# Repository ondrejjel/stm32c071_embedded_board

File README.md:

# STM32C071 Development Board

A compact, portable embedded development board built around the **STM32C071K8T6** microcontroller.

The board was designed as a personal platform for embedded firmware development, hardware experimentation, and prototyping. The focus is on providing a reasonably complete development environment in a small form factor while keeping important interfaces accessible for debugging and experimentation.

> **Status:** Rev. 1 PCB manufactured.

## Features

### MCU

* **STM32C071K8T6**
* ARM Cortex-M0+ core
* LQFP-32 package
* SWD programming and debugging
* Dedicated RESET and BOOT0 buttons

### Memory

* **16 MB SPI NOR flash**
* Winbond **W25Q128JV**
* Dedicated SPI interface
* Accessible through exposed test points

### Security

* **ATECC608A** secure element
* I²C interface
* Intended for experimentation with hardware-backed cryptography, secure key storage, and device identity

### USB

* USB-C receptacle
* USB 2.0 interface
* **USBLC6-4SC6** ESD protection

### Power

* 5 V input
* **MCP1825S-330** 3.3 V LDO
* Exposed 5 V and 3.3 V test points
* Multiple ground test points

### User Interface

* 5 user buttons
* Dedicated RESET button
* Dedicated BOOT0 button
* Dedicated red power indicator LED
* 5 user LEDs:

  * 1× red
  * 1× green
  * 1× blue
  * 1× orange
  * 1× yellow

### Debugging & Test

The board includes numerous test points to make hardware bring-up and debugging easier.

Exposed signals include:

* SWDIO
* SWCLK
* NRST
* BOOT0
* UART TX/RX
* SPI CS
* SPI CLK
* SPI DI
* SPI DO
* I²C SDA/SCL
* 5 V
* 3.3 V
* GND

An **STDC14** debug connector is also provided.

## Hardware Architecture

The main hardware blocks are:

```text
                         ┌──────────────────┐
                    -----│    USB-C Input   │
                    │    └────────┬─────────┘
                    │             │
                   USB           5 V
                    │             │
                    │    ┌────────▼─────────┐
                    │    │   Power / 3.3 V  │
                    │    │     MCP1825S     │
                    │    └────────┬─────────┘
                    │             │ 
                 ┌──▼─────────────▼────────────────┐
                 │          STM32C071K8T6           │
                 │                                 │
                 │  GPIO   SPI   I²C   USB   SWD   │
                 └───┬─────┬─────┬─────┬────┬─────┘
                     │     │     │     │    │
                     │     │     │     │    └── Debug
                     │     │     │     │
                     │     │     │     └──── USB
                     │     │     │
                     │     │     └──────── ATECC608A
                     │     │
                     │     └────────────── W25Q128JV
                     │
                     └────────────────── Buttons / LEDs
```

The exact peripheral assignments are defined in the schematic and firmware configuration.

## PCB Design

The schematic and PCB were designed entirely in **KiCad**.

The board was designed around several goals:

* compact and portable form factor
* practical access to debugging interfaces
* dedicated test points for important signals
* integrated external memory
* hardware security experimentation
* simple power architecture
* useful user I/O
* easy hardware bring-up

The PCB was manufactured by **JLCPCB**.

## Bring-up Plan

Once the assembled board is available, hardware bring-up will be performed incrementally.

### 1. Power

* Inspect the assembled PCB
* Check for shorts before applying power
* Verify 5 V input
* Verify 3.3 V regulator output
* Measure idle current consumption

### 2. MCU

* Connect through SWD
* Verify MCU identification
* Test RESET
* Verify BOOT0 operation
* Flash a minimal test program

### 3. GPIO

* Test user buttons
* Test LEDs
* Verify GPIO levels and mappings

### 4. SPI Flash

* Verify SPI signals with a logic analyzer
* Read the JEDEC ID
* Test read/write operations
* Verify the full memory interface

### 5. I²C / Secure Element

* Verify I²C electrical levels
* Detect the ATECC608A
* Establish communication
* Test basic device functionality

### 6. USB

* Verify USB power and signal integrity
* Test USB enumeration
* Develop and validate the intended USB functionality

Any hardware problems discovered during bring-up will be documented in this repository.

## Test Points

The board intentionally exposes important signals for external measurement.

| Signal     | Purpose              |
| ---------- | -------------------- |
| GND        | Ground reference     |
| 5V         | Main 5 V rail        |
| 3V3        | Regulated 3.3 V rail |
| NRST       | MCU reset            |
| BOOT0      | Boot configuration   |
| SWDIO      | SWD data             |
| SWCLK      | SWD clock            |
| TX         | UART transmit        |
| RX         | UART receive         |
| CS         | SPI chip select      |
| CLK        | SPI clock            |
| DI         | SPI data input       |
| DO         | SPI data output      |
| SDA        | I²C data             |
| SCL        | I²C clock            |
| USERBTN1–5 | User button signals  |

## Repository Structure

```text
.
├── hardware/
│   ├── schematic/
│   ├── pcb/
│   └── fabrication/
├── firmware/
├── docs/
├── LICENSE
└── README.md
```

The structure may evolve as firmware and documentation are added.

## Design Files

The KiCad project contains the complete schematic and PCB design.

Manufacturing files are included so that future revisions can be reproduced or modified.

## Bill of Materials

The main active components are:

| Reference | Component       | Purpose                     |
| --------- | --------------- | --------------------------- |
| U1        | STM32C071K8T6   | Main MCU                    |
| U2        | ATECC608A-SSHDA | Secure element              |
| U3        | W25Q128JV       | 16 MB SPI flash             |
| U4        | USBLC6-4SC6     | USB ESD protection          |
| U5        | MCP1825S-330E   | 3.3 V LDO                   |
| J1        | STDC14          | Debug/programming connector |
| J2        | USB-C           | USB/power connection        |

The complete BOM is available in the hardware project files.

## Project Status

| Area                | Status                |
| ------------------- | --------------------- |
| Schematic           | Complete              |
| PCB layout          | Complete              |
| Manufacturing files | Complete              |
| PCB manufacturing   | In progress           |
| Assembly            | Pending               |
| Hardware bring-up   | Pending               |
| Firmware            | Planned               |

## Lessons & Revision History

This is my first custom PCB project, so the first revision is also intended as a learning platform.

Rather than treating Rev. 1 as a final design, the goal is to use the board to identify:

* schematic mistakes
* layout issues
* component selection problems
* power-related issues
* signal integrity problems
* usability improvements

Findings from the first hardware revision will be documented here and used to guide future revisions.

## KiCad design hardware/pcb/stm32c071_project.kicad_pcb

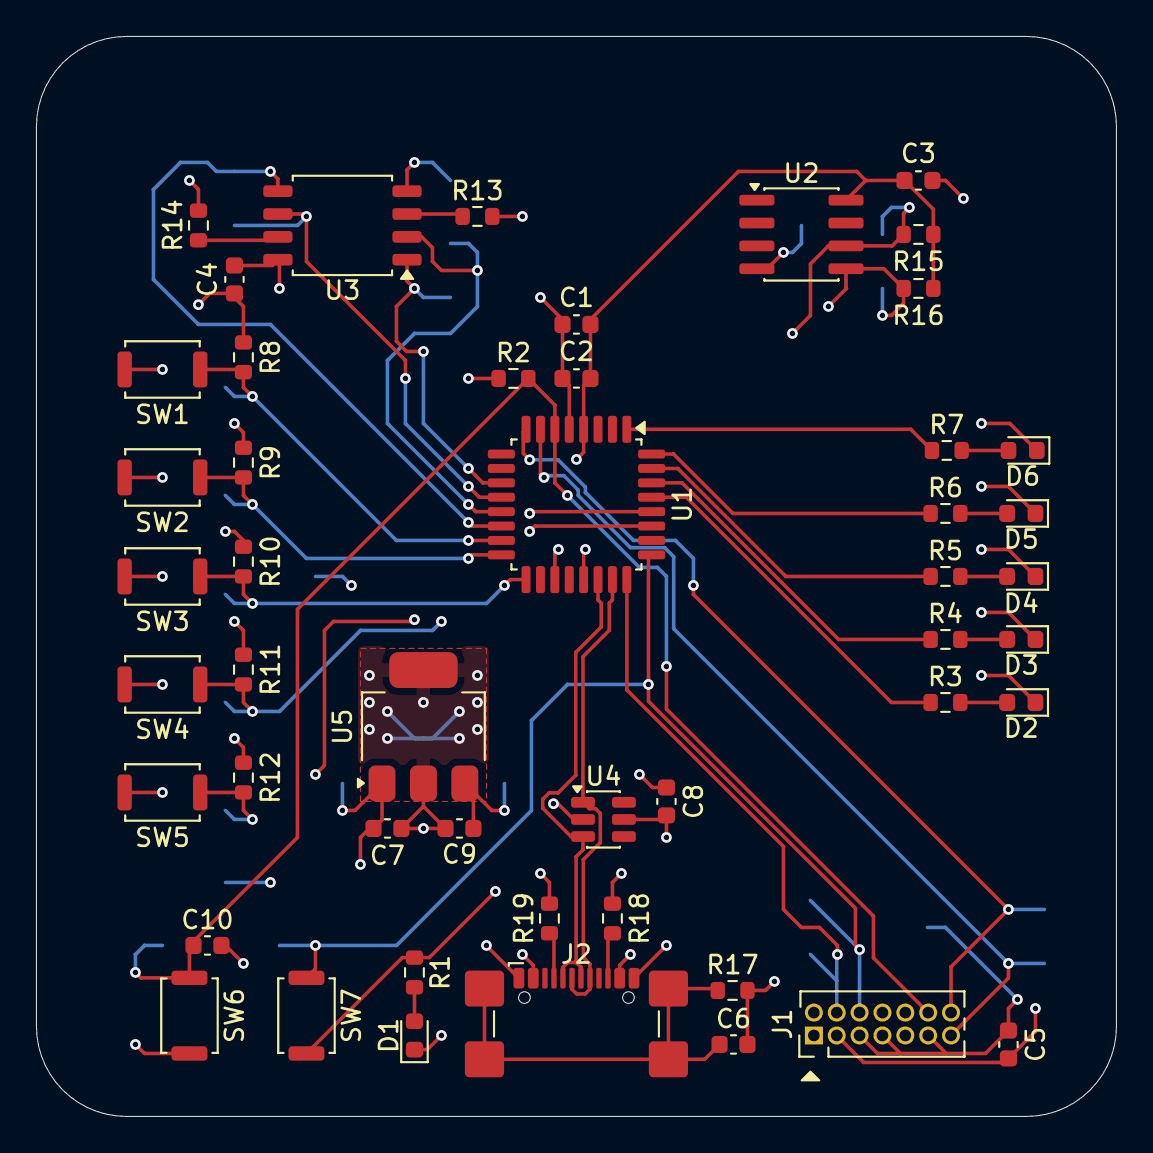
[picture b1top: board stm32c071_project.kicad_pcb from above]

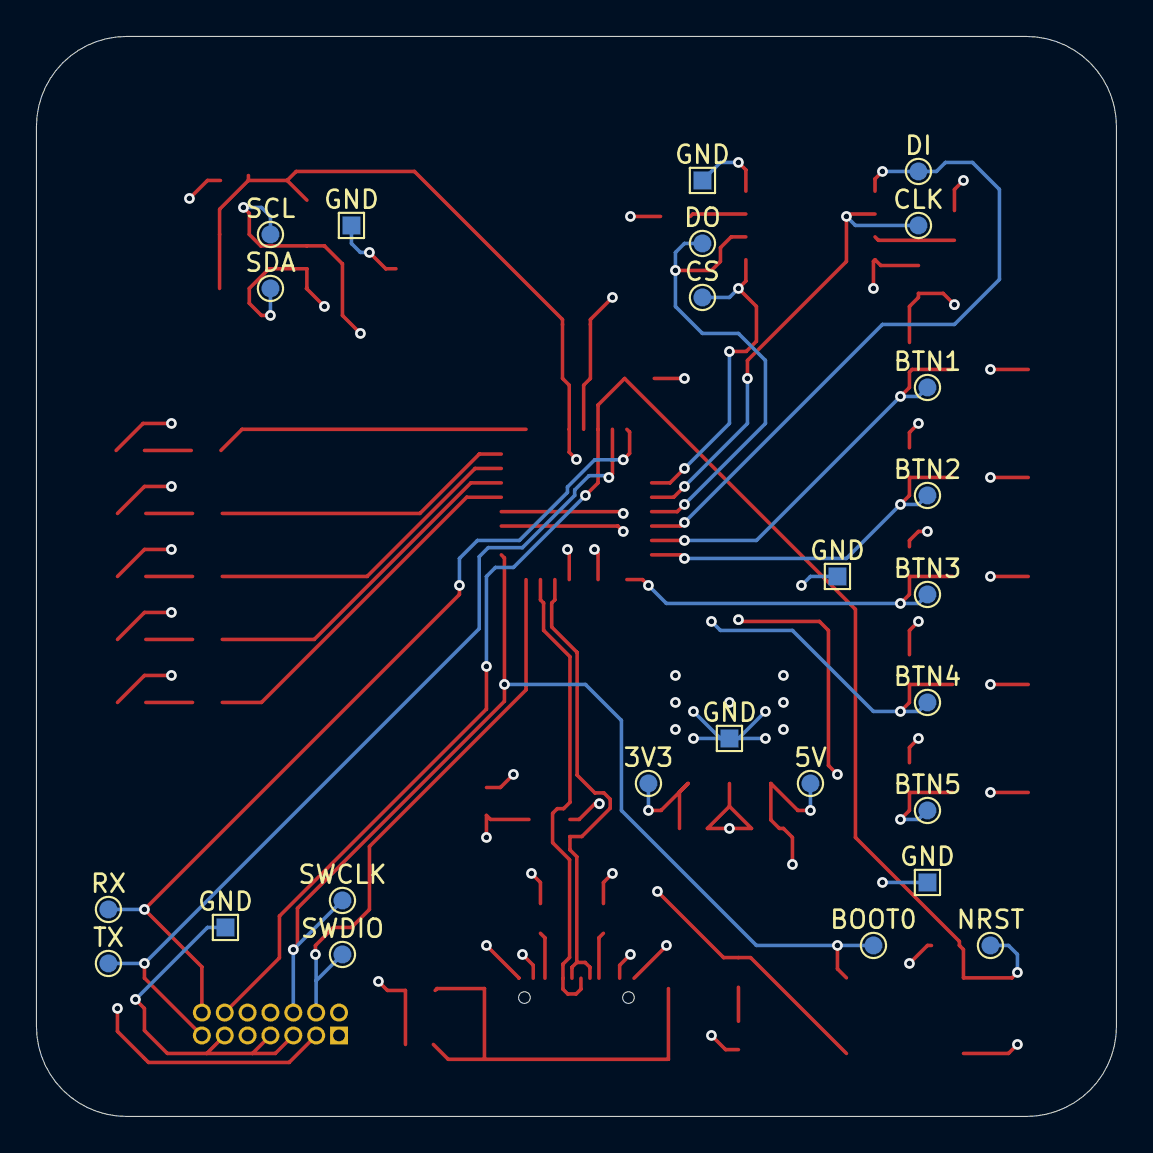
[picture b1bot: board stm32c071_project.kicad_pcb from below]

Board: 4 copper layers, 60.0 x 60.0 mm, 74 parts (25 on the bottom side), 37 nets.

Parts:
3V3: 3V3; TestPoint_Pad_D1.0mm
5V: 5V; TestPoint_Pad_D1.0mm
BOOT0: BOOT0; TestPoint_Pad_D1.0mm
BTN1: USERBTN1; TestPoint_Pad_D1.0mm
BTN2: USERBTN2; TestPoint_Pad_D1.0mm
BTN3: USERBTN3; TestPoint_Pad_D1.0mm
BTN4: USERBTN4; TestPoint_Pad_D1.0mm
BTN5: USERBTN5; TestPoint_Pad_D1.0mm
C1, C9: 1uF; C_0603_1608Metric
C2, C3, C4, C5, C6, C8, C10: 100nF; C_0603_1608Metric
C7: 4.7uF; C_0603_1608Metric
CLK: CLK; TestPoint_Pad_D1.0mm
CS: CS; TestPoint_Pad_D1.0mm
D1, D2: RED; LED_0603_1608Metric
D3: GREEN; LED_0603_1608Metric
D4: BLUE; LED_0603_1608Metric
D5: ORANGE; LED_0603_1608Metric
D6: YELLOW; LED_0603_1608Metric
DI: DI; TestPoint_Pad_D1.0mm
DO: DO; TestPoint_Pad_D1.0mm
GND: GND; TestPoint_Pad_1.0x1.0mm
GND#2, GND#3, GND#4, GND#5, GND#6: GND; TestPoint_Pad_1.0x1.0mm
J1: Conn_ST_STDC14; PinHeader_2x07_P1.27mm_Vertical
J2: USB_C_Receptacle_USB2.0_16P; USB_C_Receptacle_GCT_USB4110
NRST: NRST; TestPoint_Pad_D1.0mm
R1: 1k; R_0603_1608Metric
R2, R8, R9, R10, R11, R12: 10k; R_0603_1608Metric
R3, R4, R5, R6, R7: 470; R_0603_1608Metric
R13, R14, R15, R16: 4.7k; R_0603_1608Metric
R17: 1M; R_0603_1608Metric
R18, R19: 5.1k; R_0603_1608Metric
RX: RX; TestPoint_Pad_D1.0mm
SCL: SCL; TestPoint_Pad_D1.0mm
SDA: SDA; TestPoint_Pad_D1.0mm
SW1, SW2, SW3, SW4, SW5: SW_Push; SW_Push_SPST_NO_Alps_SKRK
SW6: RESET; SW_Push_SPST_NO_Alps_SKRK
SW7: BOOT0; SW_Push_SPST_NO_Alps_SKRK
SWCLK: SWCLK; TestPoint_Pad_D1.0mm
SWDIO: SWDIO; TestPoint_Pad_D1.0mm
TX: TX; TestPoint_Pad_D1.0mm
U1: STM32C071K8Tx; LQFP-32_7x7mm_P0.8mm
U2: ATECC608A-SSHDA; SOIC-8_3.9x4.9mm_P1.27mm
U3: W25Q128JVS; SOIC-8_5.3x5.3mm_P1.27mm
U4: USBLC6-4SC6; SOT-23-6
U5: MCP1825S-330E; SOT-223-3_TabPin2

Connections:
+3V3: 3V3.1 (1_1), C1.1, C2.1, C3.1, C4.1, C5.1, C9.1, J1.3 (VCC), R1.1, R2.1, R15.2, R16.2, SW1.2, SW2.2, SW3.2, SW4.2, SW5.2, SW7.2, U1.4 (VDD), U2.8 (VCC), U3.8 (VCC), U5.3 (VO)
DEBUG_SWCLK/BOOT0: BOOT0.1 (1_1), J1.6 (JCLK/SWCLK), SW7.1, SWCLK.1 (1_1), U1.25 (PA14)
DEBUG_SWDIO: J1.4 (JTMS/SWDIO), SWDIO.1 (1_1), U1.24 (PA13)
DEBUG_USART1_RX: J1.14 (VCP_TX), RX.1 (1_1), U1.8 (PA1)
DEBUG_USART1_TX: J1.13 (VCP_RX), TX.1 (1_1), U1.7 (PA0)
GND: C1.2, C2.2, C3.2, C4.2, C5.2, C6.2, C7.2, C8.2, C9.2, C10.2, D1.1 (K), D2.1 (K), D3.1 (K), D4.1 (K), D5.1 (K), D6.1 (K), GND.1 (1_1), GND#2.1 (1_1), GND#3.1 (1_1), GND#4.1 (1_1), GND#5.1 (1_1), GND#6.1 (1_1), J1.5 (GND), J1.7 (GND), J1.11 (GNDDetect), J2.A1 (GND), J2.A12 (GND), J2.B1 (GND), J2.B12 (GND), R8.2, R9.2, R10.2, R11.2, R12.2, R13.2, R14.2, R17.2, R18.2, R19.2, SW6.2, U1.5 (VSS), U2.4 (GND), U3.4 (GND), U4.2 (GND), U5.2 (GND)
I2C1_SCL: R16.1, SDA.1 (1_1), U1.19 (PA9), U2.5 (SDA)
I2C1_SDA: R15.1, SCL.1 (1_1), U1.21 (PA10), U2.6 (SCL)
MCU_NRST: C10.1, J1.12 (~RST), NRST.1 (1_1), R2.2, SW6.1, U1.6 (PF2)
unnamed: D1.2 (A), R1.2
unnamed: D2.2 (A), R3.2
unnamed: D3.2 (A), R4.2
unnamed: D4.2 (A), R5.2
unnamed: D5.2 (A), R6.2
unnamed: D6.2 (A), R7.2
unnamed: J2.A5 (CC1), R19.1
unnamed: J2.B5 (CC2), R18.1
unnamed: C6.1, J2.SH (SHIELD), R17.1
unnamed: R14.1, U3.7 (~HOLD/~RESET/IO_{3})
unnamed: R13.1, U3.3 (~WP/IO_{2})
SPI1_MISO: DO.1 (1_1), U1.13 (PA6), U3.2 (DO/IO_{1})
SPI1_MOSI: DI.1 (1_1), U1.14 (PA7), U3.5 (DI/IO_{0})
SPI1_NSS: CS.1 (1_1), U1.11 (PA4), U3.1 (~CS)
SPI1_SCK: CLK.1 (1_1), U1.12 (PA5), U3.6 (CLK)
USB_D+: J2.A6 (D+), J2.B6 (D+), U1.23 (PA12), U4.1 (I/O1)
USB_D-: J2.A7 (D-), J2.B7 (D-), U1.22 (PA11), U4.3 (I/O2)
USB_VBUS: 5V.1 (1_1), C7.1, C8.1, J2.A4 (VBUS), J2.A9 (VBUS), J2.B4 (VBUS), J2.B9 (VBUS), U4.5 (VBUS), U5.1 (VI)
USER_BUTTON1: BTN1.1 (1_1), R8.1, SW1.1, U1.15 (PB0)
USER_BUTTON2: BTN2.1 (1_1), R9.1, SW2.1, U1.16 (PB1)
USER_BUTTON3: BTN3.1 (1_1), R10.1, SW3.1, U1.17 (PB2)
USER_BUTTON4: BTN4.1 (1_1), R11.1, SW4.1, U1.27 (PB3)
USER_BUTTON5: BTN5.1 (1_1), R12.1, SW5.1, U1.28 (PB4)
USER_LED1: R3.1, U1.29 (PB5)
USER_LED2: R4.1, U1.30 (PB6)
USER_LED3: R5.1, U1.31 (PB7)
USER_LED4: R6.1, U1.32 (PB8)
USER_LED5: R7.1, U1.1 (PB9)
